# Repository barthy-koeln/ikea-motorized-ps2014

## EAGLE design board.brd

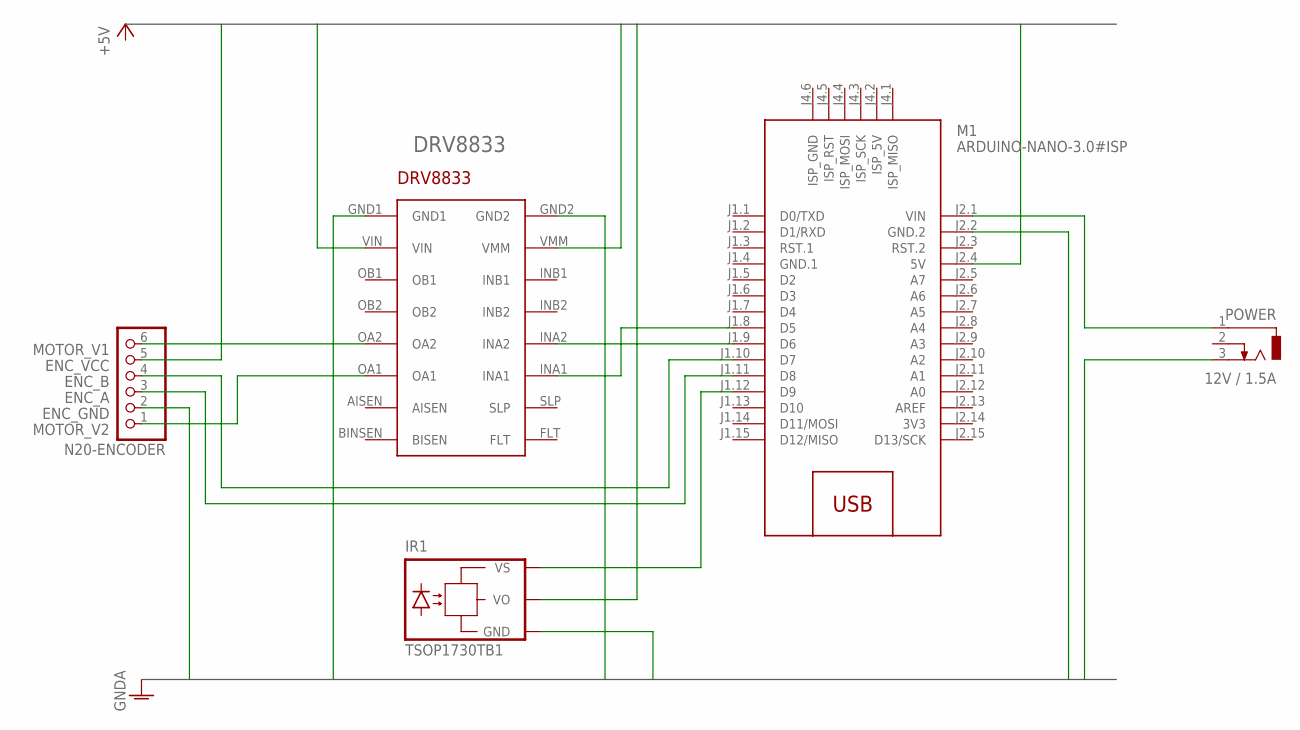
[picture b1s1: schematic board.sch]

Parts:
DRV8833: POLOLU-DRV8833
IR1: TSOP1730TB1; TSOP17_TB1
M1: ARDUINO-NANO-3.0#ISP
N20-ENCODER: PINHD-1X6; 1X06
POWER: 12V / 1.5A; DCJ0303

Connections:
3V3: M1.J2.14 (3V3)
ARDUINO_GROUND: M1.J2.2 (GND.2)
ARDUINO_VOLTAGE: M1.J2.4 (5V)
DRIVER_GROUND: DRV8833.GND1, DRV8833.GND2
DRIVER_VOLTAGE_CONTROL: DRV8833.VIN
DRIVER_VOLTAGE_MOTOR: DRV8833.VMM
ENC_A: M1.J1.11 (D8), N20-ENCODER.3
ENC_B: M1.J1.10 (D7), N20-ENCODER.4
ENC_GND: N20-ENCODER.2
ENC_VCC: N20-ENCODER.5
GND.1: M1.J1.4 (GND.1)
IR_GROUND: IR1.GND
IR_SIGNAL: IR1.VS, M1.J1.12 (D9)
IR_VOLTAGE: IR1.VO
MOTOR_CONTROL_1: DRV8833.INA1, M1.J1.8 (D5)
MOTOR_CONTROL_2: DRV8833.INA2, M1.J1.9 (D6)
MOTOR_V1: DRV8833.OA2, N20-ENCODER.6
MOTOR_V2: DRV8833.OA1, N20-ENCODER.1
POWER_GND: POWER.3
POWER_VCC: M1.J2.1 (VIN), POWER.1

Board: 2 copper layers, 5 parts (0 on the bottom side), 9 nets, no tracks yet.

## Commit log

2022-09-18 [FEATURE] prepare IR receiver
2022-09-20 [IMPROVEMENT] IR receiver and test motor commands
2022-09-20 [IMPROVEMENT] add eagle files and more program functions
2022-09-21 [IMPROVEMENT] fixed commands and one-of increments
2022-09-21 [IMPROVEMENT] remove bus and added regular net with junctions
2022-09-22 [BUGFIX] fixed offset calculation and general improvements
2022-09-22 [CHORE] cleanup up code
2022-09-22 [IMPROVEMENT] fixup second motor and calcs
2023-09-23 chore: migrate to platformIO

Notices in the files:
parts and their libraries:
diy-modules: Released under the Creative Commons Attribution 4.0 International License: http://creativecommons.org/licenses/by/4.0
